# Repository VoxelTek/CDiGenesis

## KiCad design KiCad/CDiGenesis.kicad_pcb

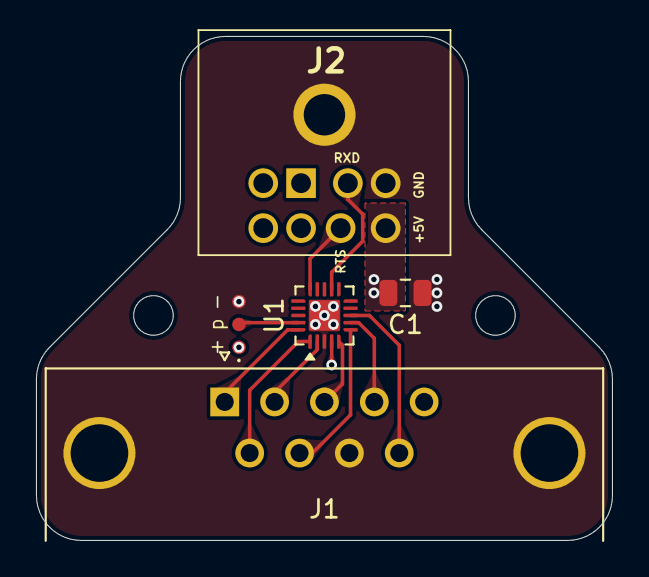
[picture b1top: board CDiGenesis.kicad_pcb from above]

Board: 2 copper layers, 32.0 x 28.0 mm, 7 parts (0 on the bottom side), 12 nets.

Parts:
C1: 1uF; C_0805_2012Metric
H1, H2: M2; MountingHole_2.2mm_M2
J1: Genesis; DSUB-9_Pins_Horizontal_P2.77x2.84mm_EdgePinOffset4.94mm_Hou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
J2: CDi; KMDGX8SN
J3: Conn_01x03; UPDI Pads
U1: ATtiny1616-M; VQFN-20-1EP_3x3mm_P0.4mm_EP1.7x1.7mm

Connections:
+5V: C1.1, J1.5, J2.8, J3.1, U1.4 (VCC)
/BTN_B/A: J1.6, U1.1 (PA2)
/BTN_C/S: J1.9, U1.8 (PA7)
/D_Down: J1.2, U1.2 (PA3)
/D_Left: J1.3, U1.5 (PA4)
/D_Right: J1.4, U1.7 (PA6)
/D_Up: J1.1, U1.20 (PA1)
/RTS: J2.7, U1.15 (PC0)
/RXD: J2.2, U1.12 (PB2)
/Select: J1.7, U1.6 (PA5)
/UPDI: J3.2, U1.19 (~RESET/PA0)
GND: C1.2, J1.0 (PAD), J1.8, J2.5, J2.MP, J3.3, U1.3 (GND), U1.21 (GND)

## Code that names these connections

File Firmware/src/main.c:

#include "main.h"
#include "console.h"

uint8_t buttonState = 0x00;
uint8_t oldButtonState = 0x00;
int8_t speeds[6] = {0x7f, 0x60, 0x40, 0x30, 0x20, 0x10};
uint8_t speedIndex = 0;
bool speedChanged = false;
const uint8_t mode = MANEUVER;

int main() {
    initPins();
    while (!gpio_read(RTS)) { // Wait for console ready

    }
    console_init(1200);
    initCDi();
    while (1) {
        loop();
    }
}

void loop() {
    refreshButtonState();

    if ((buttonState = oldButtonState) && !(buttonState & 0b00101110)) { // If no buttons have changed, AND no D-Pad movement, return.
        _delay_ms(20);
        return;
    }

    oldButtonState = buttonState;

    uint8_t b0 = 0b1000000;
	uint8_t b1 = 0b0000000;
	uint8_t b2 = 0b0000000;
    int8_t x = 0;
    int8_t y = 0;
    
    if (buttonState & 4) { // D-Pad up
        y = -speeds[speedIndex];
    }
    else if (buttonState & 16) { // D-Pad down
        y = speeds[speedIndex];
    }

    if (buttonState & 32) { // D-Pad left
        x = -speeds[speedIndex];
    }
    else if (buttonState & 64) { // D-Pad right
        x = speeds[speedIndex];
    }

    if (buttonState & 2) { // Button A, btn 1
        b0 |= 0b100000;
    }

    if (buttonState & 8) { // Button B, btn 2
        b0 |= 0b010000;
    }
        
    if (buttonState & 128) { // Button C, btn 1+2
        b0 |= 0b110000;
    }

    b0 |= ((y >> 4) & 0b1100) + (x >> 6);
    b1 |= (x & 0b111111);
    b2 |= (y & 0b111111);

    putchar(b0);
    putchar(b1);
    putchar(b2);
    _delay_ms(5);
}

void initCDi() {
    _delay_ms(100);
    putchar(mode);
}

void refreshButtonState() {
    gpio_set_high(SELECT); // Disable SELECT
    _delay_ms(3);
    buttonState = (~PORTA.IN & 0b11000000) + ((~PORTA.IN & 0b0001110) << 1); // Get D-Pad, B, C

    gpio_set_low(SELECT); // Enable SELECT
    _delay_ms(3);
    while ((PORTA.IN & 0b01010000)) { // Wait until D-Left and D-Right pressed
        
    }
    buttonState += ((~PORTA.IN & 4) >> 1) + ((~PORTA.IN & 128) >> 7); // Get A, Start
    gpio_set_high(SELECT); // Disable SELECT

    if ((buttonState & 1) && !speedChanged) { // Decrease speed value
        speedIndex = (speedIndex + 1) % 6;
        speedChanged = true;
    }
    else if (!(buttonState & 1) && speedChanged) { // Prevent rapid speed cycling
        speedChanged = false;
    }

    /*
    Bit 1 (1)   = START
    Bit 2 (2)   = A
    Bit 3 (4)   = D-Up
    Bit 4 (8)   = B
    Bit 5 (16)  = D-Down
    Bit 6 (32)  = D-Left
    Bit 7 (64)  = D-Right
    Bit 8 (128) = C
    */
}

void initPins() {
    // Set pins to input
    PORTA.DIR = 0b00000000;
    PORTA.DIRCLR = 0b01111110;
    // Set as pull-up
    PORTA.PIN1CTRL = PORT_PULLUPEN_bm;
    PORTA.PIN2CTRL = PORT_PULLUPEN_bm;
    PORTA.PIN3CTRL = PORT_PULLUPEN_bm;
    PORTA.PIN4CTRL = PORT_PULLUPEN_bm;
    PORTA.PIN6CTRL = PORT_PULLUPEN_bm;
    PORTA.PIN7CTRL = PORT_PULLUPEN_bm;

    gpio_input(RTS);

    gpio_output(SELECT);
    gpio_set_high(SELECT);
    /*
    PA0 <-- UPDI
    PA1 <-- /D-Up
    PA2 <-- /Btn B
    PA3 <-- /D-Down
    PA4 <-- /D-Left
    PA5 --> /SELECT
    PA6 <-- /D-Right
    PA7 <-- /Btn C
    */
}

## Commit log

2026-01-17 Effectively finalise PCB design
2026-01-18 Fix connector type
2026-01-19 Move into folders, begin firmware dev
2026-01-19 More firmware development
2026-01-19 More code work
2026-01-20 Add silkscreen, nearing code completion
2026-01-20 Effectively finalise code, remove SELECT nonsense
2026-01-20 Revert PCB changes, will modify code
    This reverts commit 0f8f6d9ed579b1546b77e135067905f4b0f0e6bf.
2026-01-20 Largely complete, work required for 6-button
    In the current state, the ATtiny may be polling the controller so fast that a 6-button controller would think it needs to present its additional buttons. Either this could be prevented by adding dela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
2026-01-21 Slightly increase delay
    Increase delay slightly to ensure that no issues arise if attempting to use a 6-button controller
2026-01-21 Change to 2 stop bits
2026-01-21 Switch from printf to putchar
